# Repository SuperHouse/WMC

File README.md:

Wheelchair Motor Controller
===========================

Motion controller for an electric wheelchair using 24V DC motors, such
as a Permobil F5.

Controls two wheelchair motors using a RoboClaw motor driver. It also
has outputs for a solenoid braking system, and a CAN bus interface to
communicate with other modules on the chair.

Features:

 * Takes power from the chair battery.
 * Mounting location for RoboClaw motor driver.
 * Communicates with RoboClaw using serial commands.
 * MOSFETs to release mechanical brakes.
 * CAN bus.

More information is available at:

  https://www.superhouse.tv/wmc

Hardware
--------
The "Hardware" directory contains the PCB design as an EAGLE project.
EAGLE PCB design software is available from Autodesk free for
non-commercial use.

Firmware
--------
The "Firmware" directory contains example firmware as an Arduino
project.

Credits
-------
 * Jonathan Oxer <jon@oxer.com.au>
 * Chris Fryer <chris.fryer78@gmail.com>

License
-------
Copyright 2019-2020 SuperHouse Automation Pty Ltd  www.superhouse.tv  

The hardware portion of this project is licensed under the TAPR Open
Hardware License (www.tapr.org/OHL). The "license" folder within this
repository contains a copy of this license in plain text format.

The software portion of this project is licensed under the Simplified
BSD License. The "licence" folder within this project contains a
copy of this license in plain text format.

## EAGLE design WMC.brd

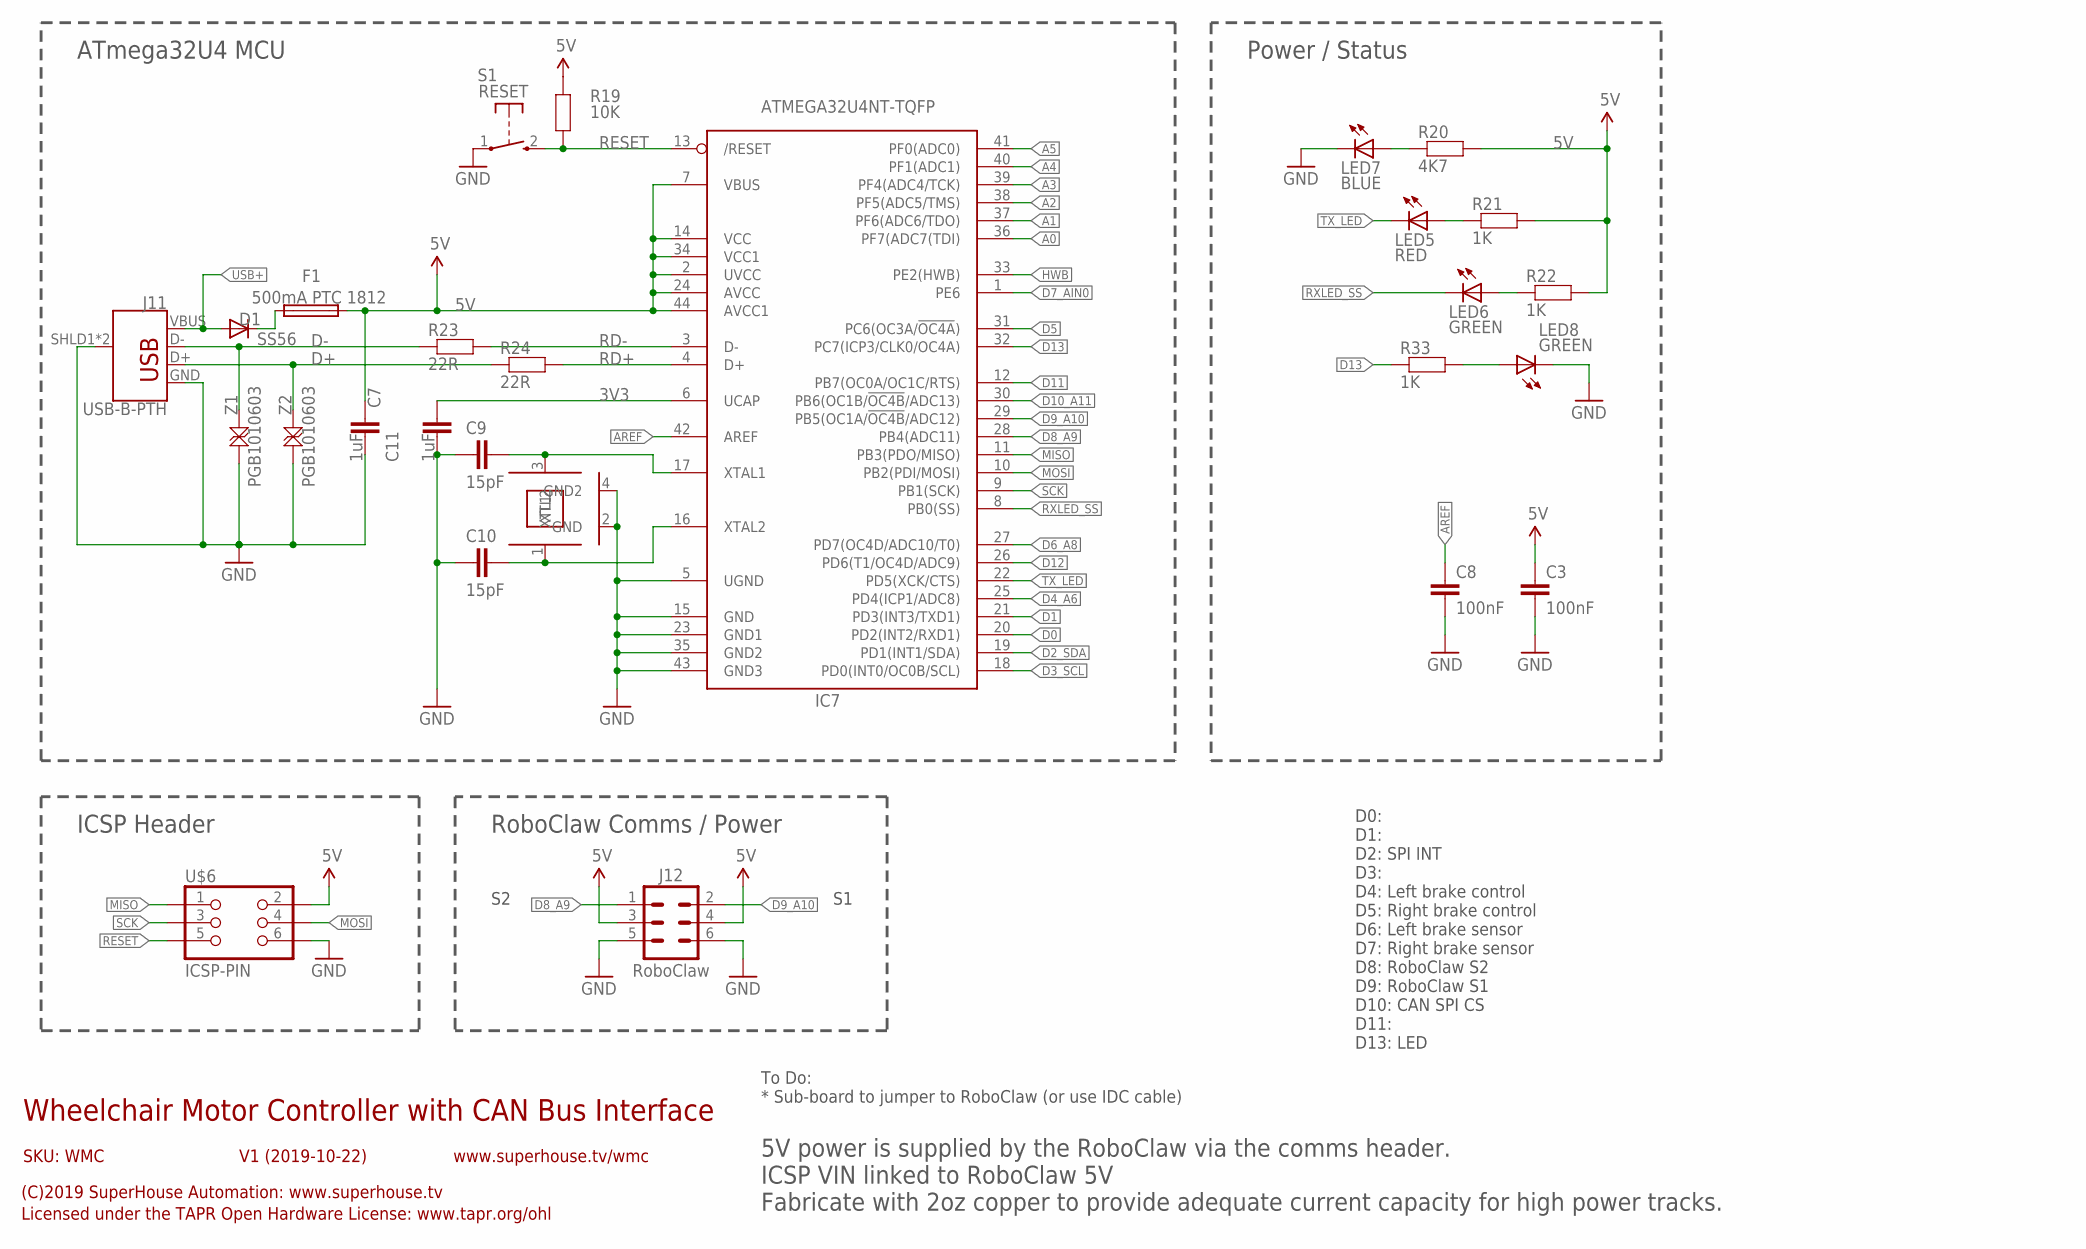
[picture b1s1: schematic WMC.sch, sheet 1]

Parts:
C3, C8: 100nF; C0603
C7, C11: 1uF; C0603
C9, C10: 15pF; C0603
D1: SS56; SMA-DIODE
F1: 500mA PTC 1812; 1812
IC7: ATMEGA32U4NT-TQFP; TQFP44
J11: USB-B-PTH
J12: RoboClaw; 2X03-P
LED5: RED; LED-0603
LED6, LED8: GREEN; LED-0603
LED7: BLUE; LED-0603
R19: 10K; R0603
R20: 4K7; R0603
R21, R22, R33: 1K; R0603
R23, R24: 22R; R0603
S1: RESET; TACTILE_SMT_3X4X2
U$6: ICSP-PIN; 2X03-ICSP
XTL2: 16MHz; CRYSTAL-SMD-3X2
Z1, Z2: PGB1010603; TVS0603

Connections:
3V3: C11.2, IC7.6 (UCAP)
5V: C3.1, C7.1, F1.2, IC7.2 (UVCC), IC7.7 (VBUS), IC7.14 (VCC), IC7.24 (AVCC), IC7.34 (VCC1), IC7.44 (AVCC1), J12.3, J12.4, R19.2, R20.2, R21.2, R22.2, U$6.2; also elsewhere on the board
A0: IC7.36 (PF7(ADC7(TDI))
A1: IC7.37 (PF6(ADC6/TDO))
A2: IC7.38 (PF5(ADC5/TMS))
A3: IC7.39 (PF4(ADC4/TCK))
A4: IC7.40 (PF1(ADC1))
A5: IC7.41 (PF0(ADC0))
AREF: C8.1, IC7.42 (AREF)
D0: IC7.20 (PD2(INT2/RXD1))
D1: IC7.21 (PD3(INT3/TXD1))
D2_SDA: IC7.19 (PD1(INT1/SDA)); also elsewhere on the board
D3_SCL: IC7.18 (PD0(INT0/OC0B/SCL))
D4_A6: IC7.25 (PD4(ICP1/ADC8)); also elsewhere on the board
D5: IC7.31 (PC6(OC3A/!OC4A!)); also elsewhere on the board
D6_A8: IC7.27 (PD7(OC4D/ADC10/T0)); also elsewhere on the board
D7_AIN0: IC7.1 (PE6); also elsewhere on the board
D8_A9: IC7.28 (PB4(ADC11)), J12.1
D9_A10: IC7.29 (PB5(OC1A/!OC4B!/ADC12)), J12.2
D10_A11: IC7.30 (PB6(OC1B/!OC4B!/ADC13)); also elsewhere on the board
D11: IC7.12 (PB7(OC0A/OC1C/RTS))
D12: IC7.26 (PD6(T1/OC4D/ADC9))
D13: IC7.32 (PC7(ICP3/CLK0/OC4A)), R33.1
D+: J11.D+, R24.1, Z2.2
D-: J11.D-, R23.1, Z1.2
GND: C3.2, C7.2, C8.2, C9.1, C10.1, C11.1, IC7.5 (UGND), IC7.15 (GND), IC7.23 (GND1), IC7.35 (GND2), IC7.43 (GND3), J11.GND, J11.SHLD1 (SHIELD), J11.SHLD2 (SHIELD), J12.5, J12.6, LED7.C, LED8.C, S1.1, U$6.6, XTL2.2 (GND), XTL2.4 (GND2), Z1.1, Z2.1; also elsewhere on the board
HWB: IC7.33 (PE2(HWB))
MISO: IC7.11 (PB3(PDO/MISO)), U$6.1; also elsewhere on the board
MOSI: IC7.10 (PB2(PDI/MOSI)), U$6.4; also elsewhere on the board
unnamed: C9.2, IC7.17 (XTAL1), XTL2.3 (XTL2)
unnamed: C10.2, IC7.16 (XTAL2), XTL2.1 (XTL1)
unnamed: LED7.A, R20.1
unnamed: LED5.A, R21.1
unnamed: LED6.A, R22.1
unnamed: D1.C, F1.1
unnamed: LED8.A, R33.2
RD+: IC7.4 (D+), R24.2
RD-: IC7.3 (D-), R23.2
RESET: IC7.13 (/RESET), R19.1, S1.2 (S), U$6.5
RXLED_SS: IC7.8 (PB0(SS)), LED6.C
SCK: IC7.9 (PB1(SCK)), U$6.3; also elsewhere on the board
TX_LED: IC7.22 (PD5(XCK/CTS)), LED5.C
USB+: D1.A, J11.VBUS

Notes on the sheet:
Wheelchair Motor Controller with CAN Bus Interface
V1 (2019-10-22)
SKU: WMC
(C)2019 SuperHouse Automation: www.superhouse.tv
Licensed under the TAPR Open Hardware License: www.tapr.org/ohl
www.superhouse.tv/wmc
To Do: * Sub-board to jumper to RoboClaw (or use IDC cable)
ATmega32U4 MCU
Power / Status
ICSP Header
RoboClaw Comms / Power
5V power is supplied by the RoboClaw via the comms header. ICSP VIN linked to RoboClaw 5V Fabricate with 2oz copper to provide adequate current capacity for high power tracks.
D0: D1: D2: SPI INT D3: D4: Left brake control D5: Right brake control D6: Left brake sensor D7: Right brake sensor D8: RoboClaw S2 D9: RoboClaw S1 D10: CAN SPI CS D11: D13: LED

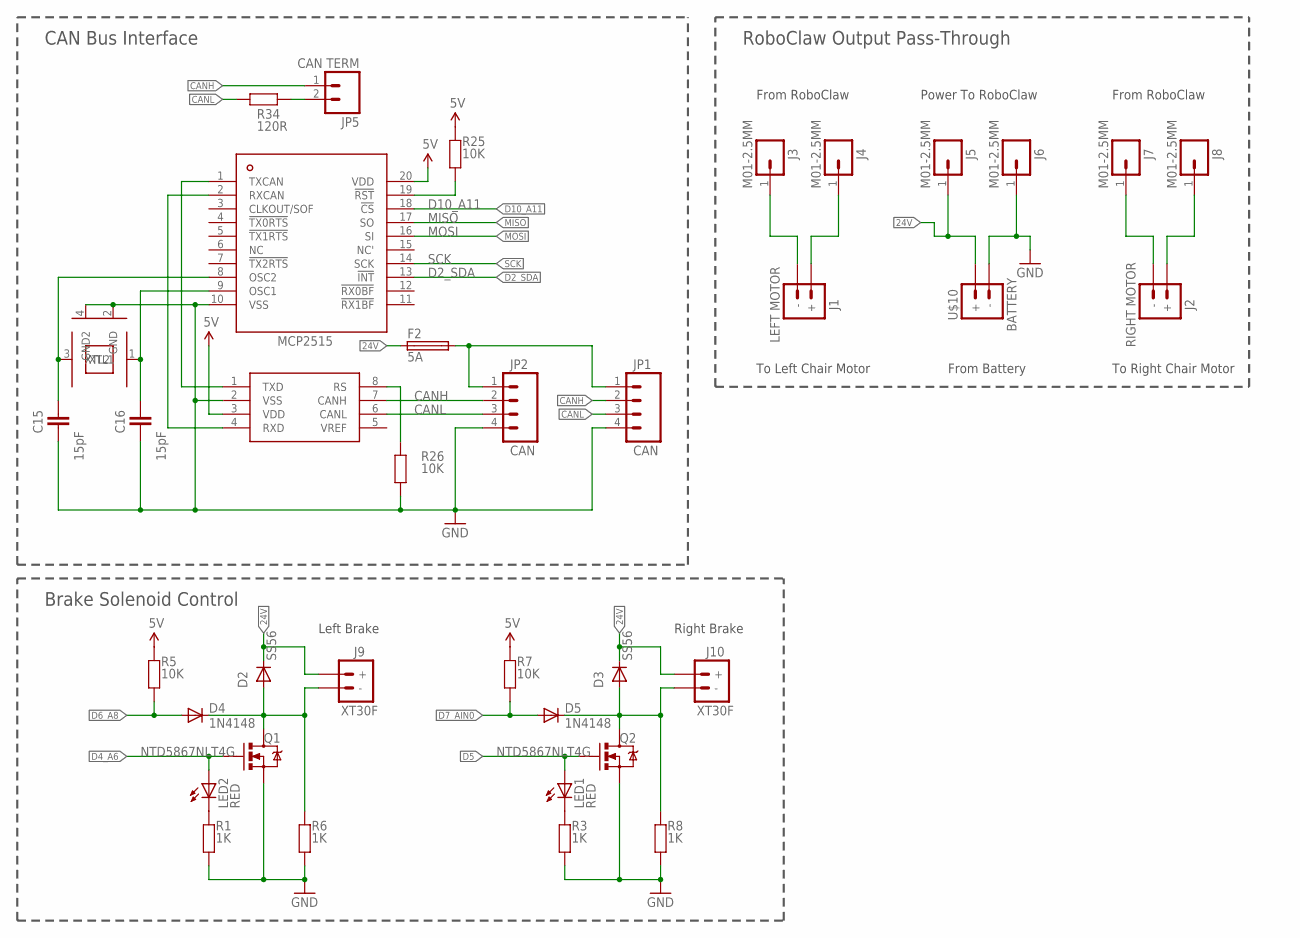
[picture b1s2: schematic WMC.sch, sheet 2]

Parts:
C15, C16: 15pF; C0603
D2, D3: SS56; SMA-DIODE
D4, D5: 1N4148; SOD-323
F2: 5A; MCCQ-122
IC5: MCP2551; SO08
IC6: MCP2515; TSSOP20
J1: LEFT MOTOR; XT60PW-F
J2: RIGHT MOTOR; XT60PW-F
J3, J4, J5, J6, J7, J8: M01-2.5MM; 1X01-2.5MM
J9, J10: XT30F; XT30PW-F
JP1, JP2: CAN; 1X04-P
JP5: CAN TERM; 1X02-P
LED1, LED2: RED; LED-0603
Q1, Q2: NTD5867NLT4G; DPACK
R1, R3, R6, R8: 1K; R0603
R5, R7, R25, R26: 10K; R0603
R34: 120R; R0603
U$10: BATTERY; XT90PW-M
XTL4: 16MHz; CRYSTAL-SMD-3X2

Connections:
5V: IC5.3 (VDD), IC6.20 (VDD), R5.2, R7.2, R25.2; also elsewhere on the board
24V: D2.C, D3.C, F2.1, F2.2 (1), J5.1, J9.+, J10.+, U$10.+
CANH: IC5.7 (CANH), JP1.2, JP2.2, JP5.1
CANL: IC5.6 (CANL), JP1.3, JP2.3, R34.1
D2_SDA: IC6.13 (!INT); also elsewhere on the board
D4_A6: LED2.A, Q1.1 (G); also elsewhere on the board
D5: LED1.A, Q2.1 (G); also elsewhere on the board
D6_A8: D4.2 (A), R5.1; also elsewhere on the board
D7_AIN0: D5.2 (A), R7.1; also elsewhere on the board
D10_A11: IC6.18 (!CS); also elsewhere on the board
GND: C15.1, C16.1, IC5.2 (VSS), IC6.10 (VSS), J6.1, JP1.4, JP2.4, Q1.3 (S), Q2.3 (S), R1.1, R3.1, R6.1, R8.1, R26.1, U$10.-, XTL4.2 (GND), XTL4.4 (GND2); also elsewhere on the board
LEFT_BRAKE: D2.A, D4.1 (C), J9.-, Q1.2 (D), R6.2
MISO: IC6.17 (SO); also elsewhere on the board
MOSI: IC6.16 (SI); also elsewhere on the board
unnamed: LED2.C, R1.2
unnamed: F2.3 (2), F2.4 (2), JP1.1, JP2.1
unnamed: J1.+, J4.1
unnamed: LED1.C, R3.2
unnamed: J1.-, J3.1
unnamed: J2.-, J7.1
unnamed: J2.+, J8.1
unnamed: IC6.19 (!RST), R25.1
unnamed: IC5.1 (TXD), IC6.1 (TXCAN)
unnamed: IC5.4 (RXD), IC6.2 (RXCAN)
unnamed: IC5.8 (RS), R26.2
unnamed: C15.2, IC6.8 (OSC2), XTL4.3 (XTL2)
unnamed: C16.2, IC6.9 (OSC1), XTL4.1 (XTL1)
unnamed: JP5.2, R34.2
RIGHT_BRAKE: D3.A, D5.1 (C), J10.-, Q2.2 (D), R8.2
SCK: IC6.14 (SCK); also elsewhere on the board

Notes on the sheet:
RoboClaw Output Pass-Through
CAN Bus Interface
Brake Solenoid Control
Left Brake
Right Brake
From RoboClaw
From Battery
To Right Chair Motor
To Left Chair Motor
Power To RoboClaw

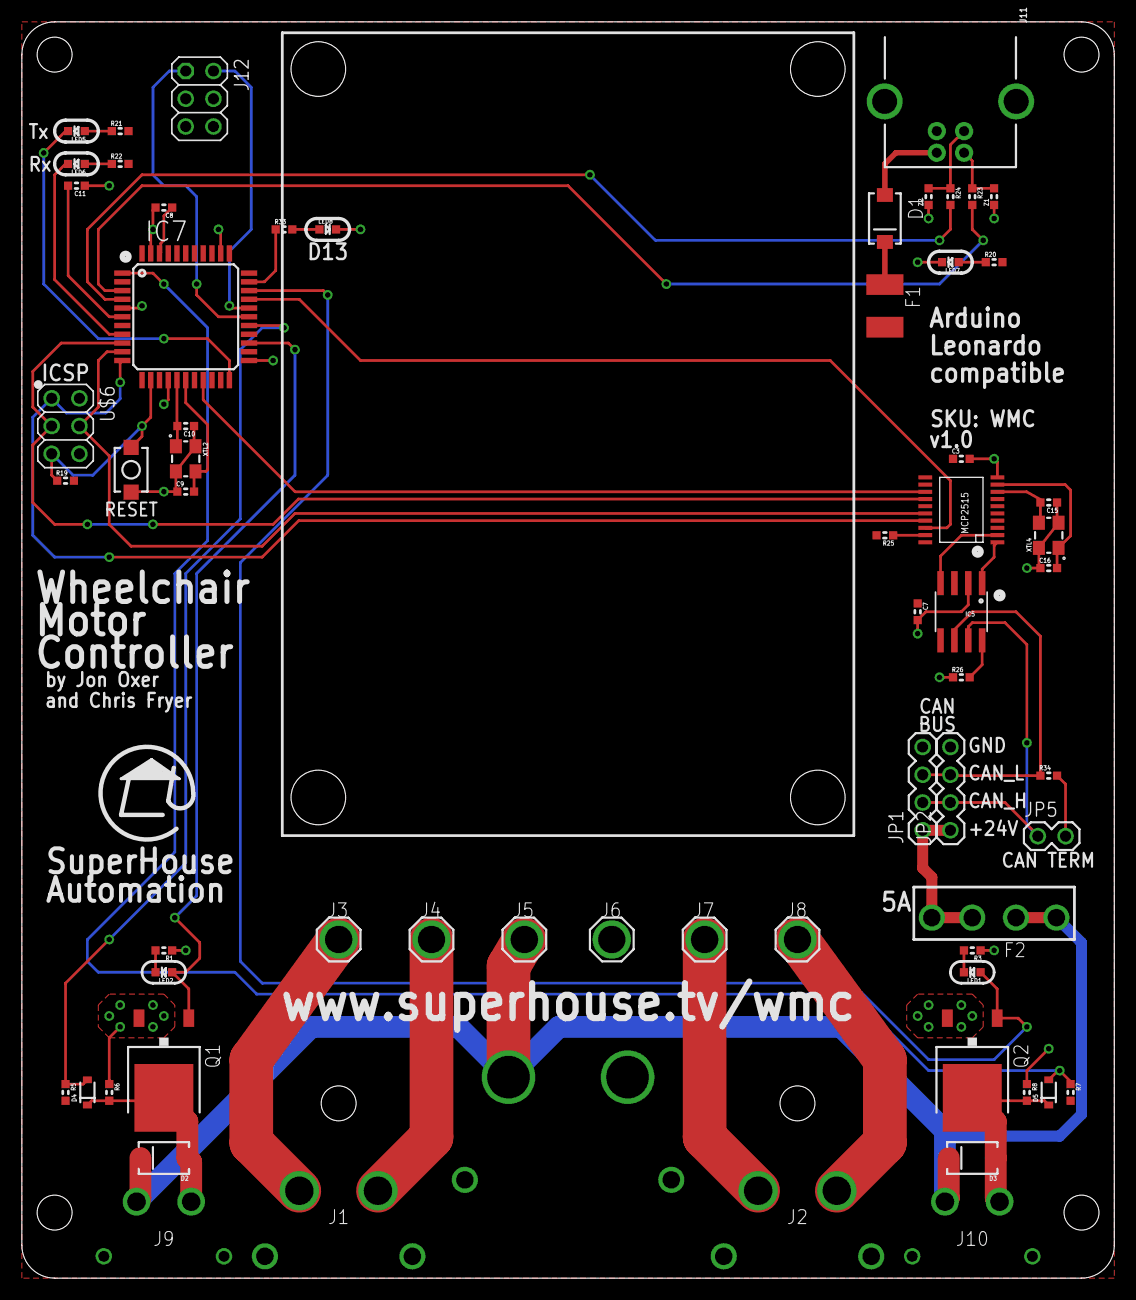
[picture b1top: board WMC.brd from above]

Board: 2 copper layers, 100.0 x 115.0 mm, 64 parts (0 on the bottom side), 50 nets.

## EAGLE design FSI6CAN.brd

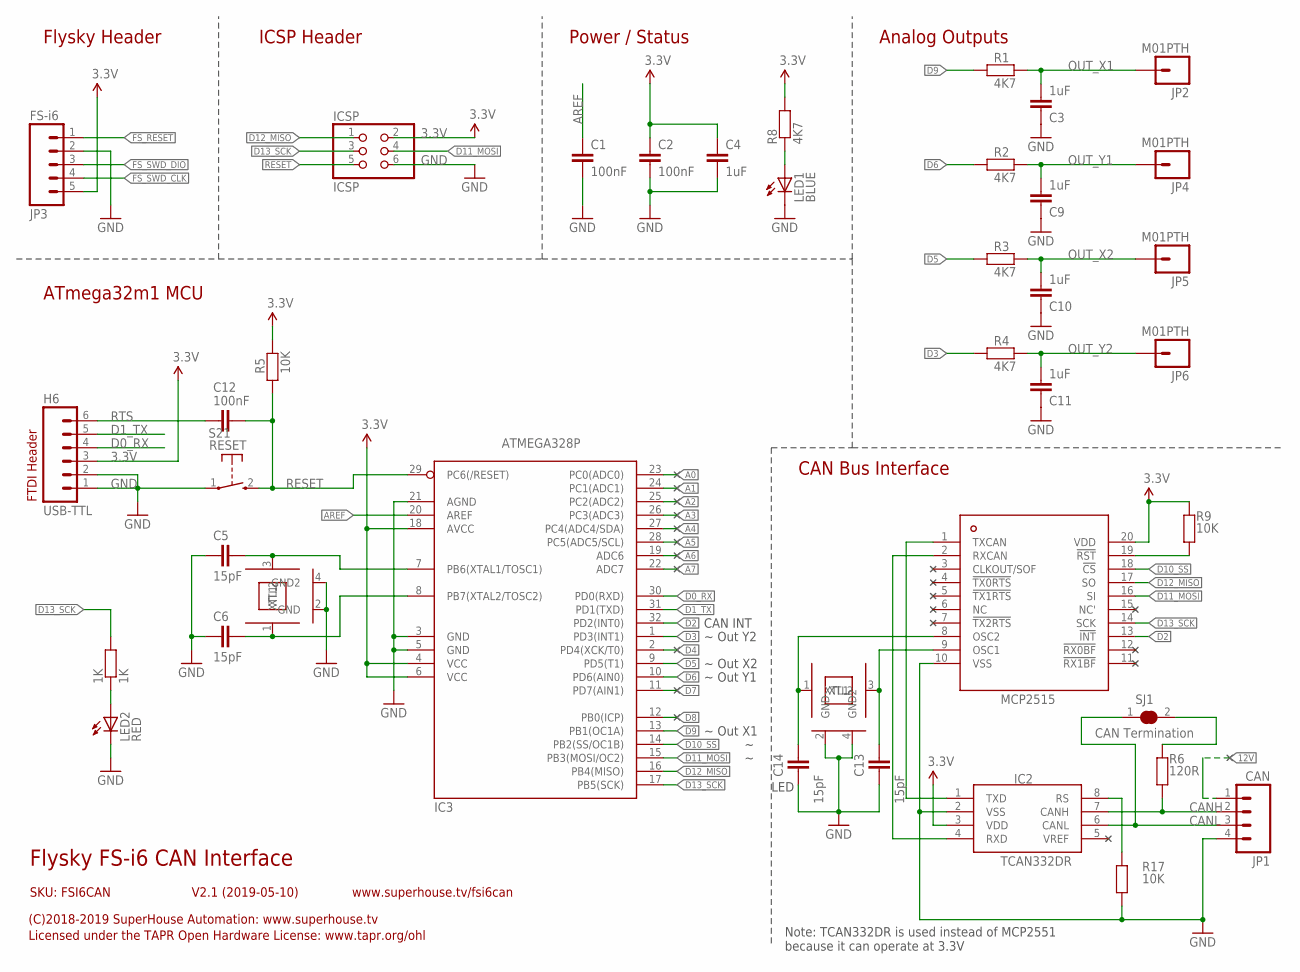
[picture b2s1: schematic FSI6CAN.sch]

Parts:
1K: 1K; R0603
C1: 100nF; C0603
C2, C12: 100nF; 0603
C3, C9, C10, C11: 1uF; C0603
C4: 1uF; 0603
C5, C6, C13, C14: 15pF; C0603
H6: USB-TTL; 1X06
IC2: TCAN332DR; SO08
IC3: ATMEGA328P; TQFP32-08
IC4: MCP2515; TSSOP20
ICSP: ICSP; 2X03
JP1: CAN; 1X04
JP2, JP4, JP5, JP6: M01PTH; 1X01
JP3: FS-i6; 1X05
LED1: BLUE; LED-0603
LED2: RED; LED-0603
R1, R2, R3, R4: 4K7; R0603
R5: 10K; 0603
R6: 120R; 0603
R8: 4K7; 0603
R9, R17: 10K; R0603
S21: RESET; TACTILE_SMT_3X4X2
SJ1: CAN Termination; SJC
XTL1: 8MHz; CRYSTAL-SMD-3X2
XTL3: 16MHz; CRYSTAL-SMD-3X2

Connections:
3.3V: C2.1, C4.1, H6.3, IC2.3 (VDD), IC3.4 (VCC), IC3.6 (VCC), IC3.18 (AVCC), IC4.20 (VDD), ICSP.2, JP3.5, R5.1, R8.2, R9.2
12V: JP1.1
A0: IC3.23 (PC0(ADC0))
A1: IC3.24 (PC1(ADC1))
A2: IC3.25 (PC2(ADC2))
A3: IC3.26 (PC3(ADC3))
A4: IC3.27 (PC4(ADC4/SDA))
A5: IC3.28 (PC5(ADC5/SCL))
A6: IC3.19 (ADC6)
A7: IC3.22 (ADC7)
AREF: C1.1, IC3.20 (AREF)
CANH: IC2.7 (CANH), JP1.2, R6.1
CANL: IC2.6 (CANL), JP1.3, SJ1.1
D0_RX: H6.4, IC3.30 (PD0(RXD))
D1_TX: H6.5, IC3.31 (PD1(TXD))
D2: IC3.32 (PD2(INT0)), IC4.13 (!INT)
D3: IC3.1 (PD3(INT1)), R4.1
D4: IC3.2 (PD4(XCK/T0))
D5: IC3.9 (PD5(T1)), R3.1
D6: IC3.10 (PD6(AIN0)), R2.1
D7: IC3.11 (PD7(AIN1))
D8: IC3.12 (PB0(ICP))
D9: IC3.13 (PB1(OC1A)), R1.1
D10_SS: IC3.14 (PB2(SS/OC1B)), IC4.18 (!CS)
D11_MOSI: IC3.15 (PB3(MOSI/OC2)), IC4.16 (SI), ICSP.4
D12_MISO: IC3.16 (PB4(MISO)), IC4.17 (SO), ICSP.1
D13_SCK: 1K.2, IC3.17 (PB5(SCK)), IC4.14 (SCK), ICSP.3
FS_RESET: JP3.1
FS_SWD_CLK: JP3.4
FS_SWD_DIO: JP3.3
GND: C1.2, C2.2, C3.2, C4.2, C5.1, C6.1, C9.2, C10.2, C11.2, C13.1, C14.1, H6.1, H6.2, IC2.2 (VSS), IC3.3 (GND), IC3.5 (GND), IC3.21 (AGND), IC4.10 (VSS), ICSP.6, JP1.4, JP3.2, LED1.C, LED2.C, R17.1, S21.1, XTL1.2 (GND), XTL1.4 (GND2), XTL3.2 (GND), XTL3.4 (GND2)
unnamed: 1K.1, LED2.A
unnamed: R6.2, SJ1.2
unnamed: IC2.1 (TXD), IC4.1 (TXCAN)
unnamed: LED1.A, R8.1
unnamed: IC2.4 (RXD), IC4.2 (RXCAN)
unnamed: C13.2, IC4.9 (OSC1), XTL3.3 (XTL2)
unnamed: C14.2, IC4.8 (OSC2), XTL3.1 (XTL1)
unnamed: C5.2, IC3.7 (PB6(XTAL1/TOSC1)), XTL1.3 (XTL2)
unnamed: C6.2, IC3.8 (PB7(XTAL2/TOSC2)), XTL1.1 (XTL1)
unnamed: IC2.8 (RS), R17.2
unnamed: IC4.19 (!RST), R9.1
OUT_X1: C3.1, JP2.1, R1.2
OUT_X2: C10.1, JP5.1, R3.2
OUT_Y1: C9.1, JP4.1, R2.2
OUT_Y2: C11.1, JP6.1, R4.2
RESET: C12.2, IC3.29 (PC6(/RESET)), ICSP.5, R5.2, S21.2 (S)
RTS: C12.1, H6.6

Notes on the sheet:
ATmega32m1 MCU
Flysky FS-i6 CAN Interface
V2.1 (2019-05-10)
SKU: FSI6CAN
(C)2018-2019 SuperHouse Automation: www.superhouse.tv
Licensed under the TAPR Open Hardware License: www.tapr.org/ohl
www.superhouse.tv/fsi6can
Power / Status
FTDI Header
Flysky Header
Analog Outputs
CAN Bus Interface
ICSP Header
~ Out Y2
~ Out X2
~ Out Y1
LED
Note: TCAN332DR is used instead of MCP2551 because it can operate at 3.3V
CAN INT
~ Out X1

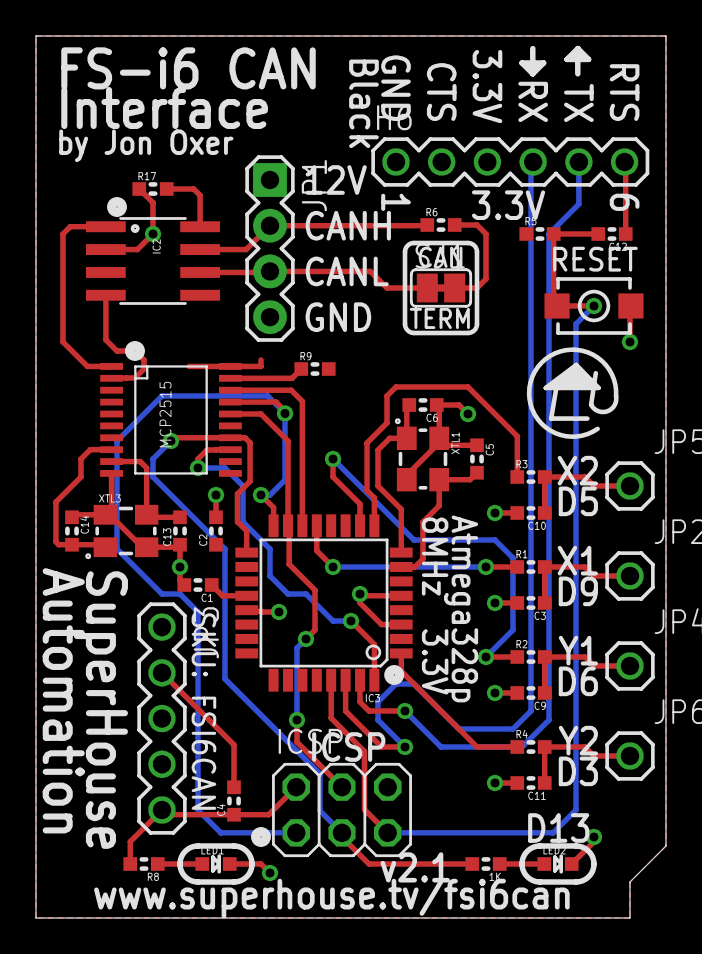
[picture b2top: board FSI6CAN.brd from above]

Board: 2 copper layers, 35.0 x 49.0 mm, 39 parts (0 on the bottom side), 33 nets.

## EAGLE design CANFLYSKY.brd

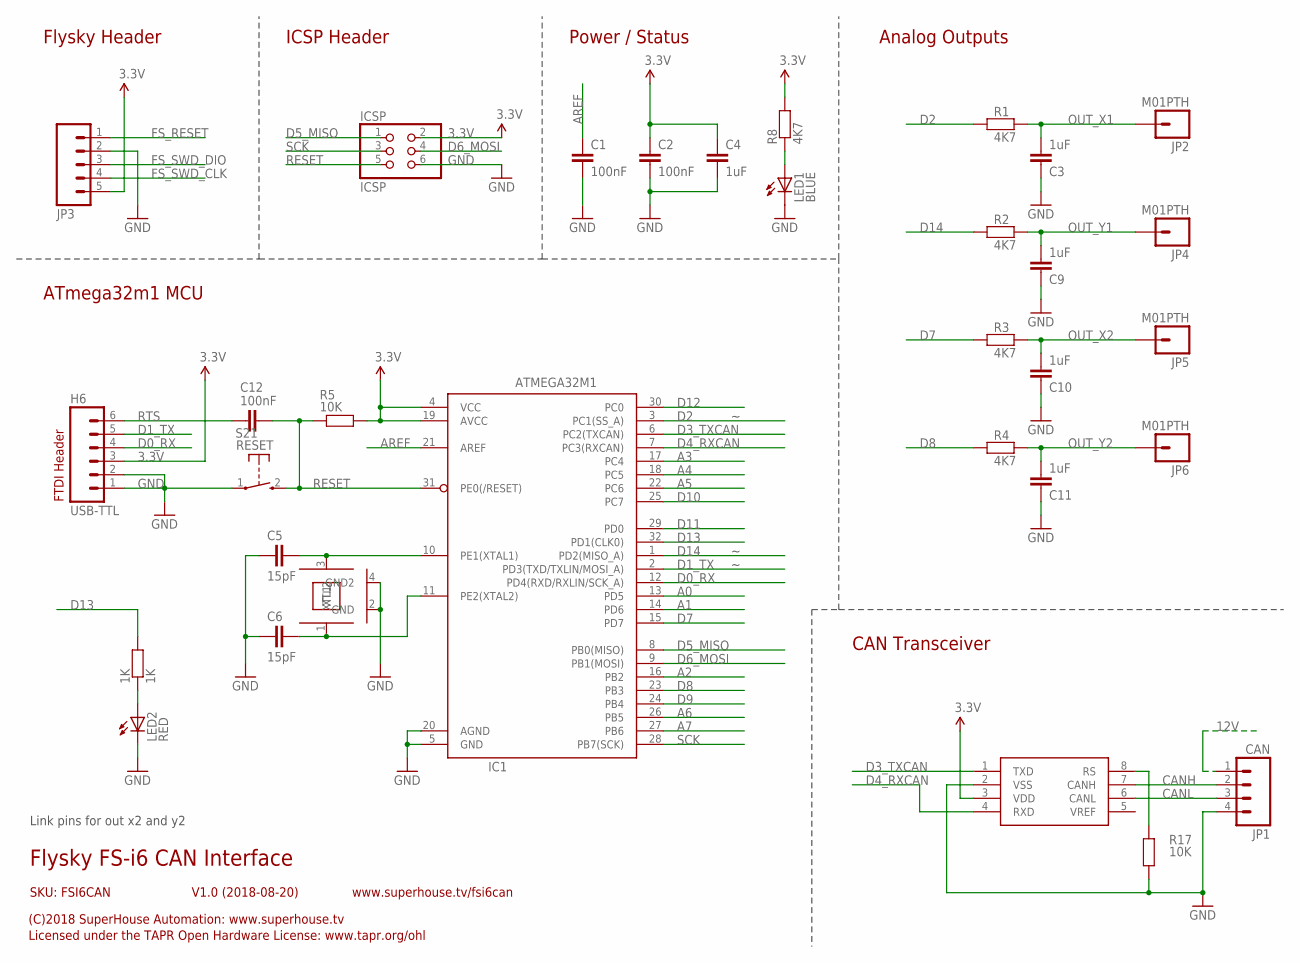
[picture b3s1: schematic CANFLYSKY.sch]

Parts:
1K: 1K; 0603
C1, C2, C12: 100nF; 0603
C3, C4, C9, C10, C11: 1uF; 0603
C5, C6: 15pF; 0603
H6: USB-TTL; 1X06
IC1: ATMEGA32M1; TQFP32-08
ICSP: ICSP; 2X03
JP1: CAN; 1X04
JP2, JP4, JP5, JP6: M01PTH; 1X01
JP3: M05PTH; 1X05
LED1: BLUE; LED-0603
LED2: RED; LED-0603
R1, R2, R3, R4, R8: 4K7; 0603
R5, R17: 10K; 0603
S21: RESET; TACTILE_SWITCH_SMD_2PIN_TINY
U1: MCP2551; SO08
XTL1: 8MHz; CRYSTAL-SMD-3X2

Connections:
3.3V: C2.1, C4.1, H6.3, IC1.4 (VCC), IC1.19 (AVCC), ICSP.2, JP3.5, R5.1, R8.2, U1.3 (VDD)
12V: JP1.1
A0: IC1.13 (PD5)
A1: IC1.14 (PD6)
A2: IC1.16 (PB2)
A3: IC1.17 (PC4)
A4: IC1.18 (PC5)
A5: IC1.22 (PC6)
A6: IC1.26 (PB5)
A7: IC1.27 (PB6)
AREF: C1.1, IC1.21 (AREF)
CANH: JP1.2, U1.7 (CANH)
CANL: JP1.3, U1.6 (CANL)
D0_RX: H6.4, IC1.12 (PD4(RXD/RXLIN/SCK_A))
D1_TX: H6.5, IC1.2 (PD3(TXD/TXLIN/MOSI_A))
D2: IC1.3 (PC1(SS_A)), R1.1
D3_TXCAN: IC1.6 (PC2(TXCAN)), U1.1 (TXD)
D4_RXCAN: IC1.7 (PC3(RXCAN)), U1.4 (RXD)
D5_MISO: IC1.8 (PB0(MISO)), ICSP.1
D6_MOSI: IC1.9 (PB1(MOSI)), ICSP.4
D7: IC1.15 (PD7), R3.1
D8: IC1.23 (PB3), R4.1
D9: IC1.24 (PB4)
D10: IC1.25 (PC7)
D11: IC1.29 (PD0)
D12: IC1.30 (PC0)
D13: 1K.2, IC1.32 (PD1(CLK0))
D14: IC1.1 (PD2(MISO_A)), R2.1
FS_RESET: JP3.1
FS_SWD_CLK: JP3.4
FS_SWD_DIO: JP3.3
GND: C1.2, C2.2, C3.2, C4.2, C5.1, C6.1, C9.2, C10.2, C11.2, H6.1, H6.2, IC1.5 (GND), IC1.20 (AGND), ICSP.6, JP1.4, JP3.2, LED1.C, LED2.C, R17.1, S21.1, U1.2 (VSS), XTL1.2 (GND), XTL1.4 (GND2)
unnamed: 1K.1, LED2.A
unnamed: LED1.A, R8.1
unnamed: C5.2, IC1.10 (PE1(XTAL1)), XTL1.3 (XTL2)
unnamed: C6.2, IC1.11 (PE2(XTAL2)), XTL1.1 (XTL1)
unnamed: R17.2, U1.8 (RS)
OUT_X1: C3.1, JP2.1, R1.2
OUT_X2: C10.1, JP5.1, R3.2
OUT_Y1: C9.1, JP4.1, R2.2
OUT_Y2: C11.1, JP6.1, R4.2
RESET: C12.2, IC1.31 (PE0(/RESET)), ICSP.5, R5.2, S21.2 (S)
RTS: C12.1, H6.6
SCK: IC1.28 (PB7(SCK)), ICSP.3

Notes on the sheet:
ATmega32m1 MCU
Flysky FS-i6 CAN Interface
V1.0 (2018-08-20)
SKU: FSI6CAN
(C)2018 SuperHouse Automation: www.superhouse.tv
Licensed under the TAPR Open Hardware License: www.tapr.org/ohl
www.superhouse.tv/fsi6can
Power / Status
FTDI Header
Flysky Header
Analog Outputs
CAN Transceiver
ICSP Header
Link pins for out x2 and y2

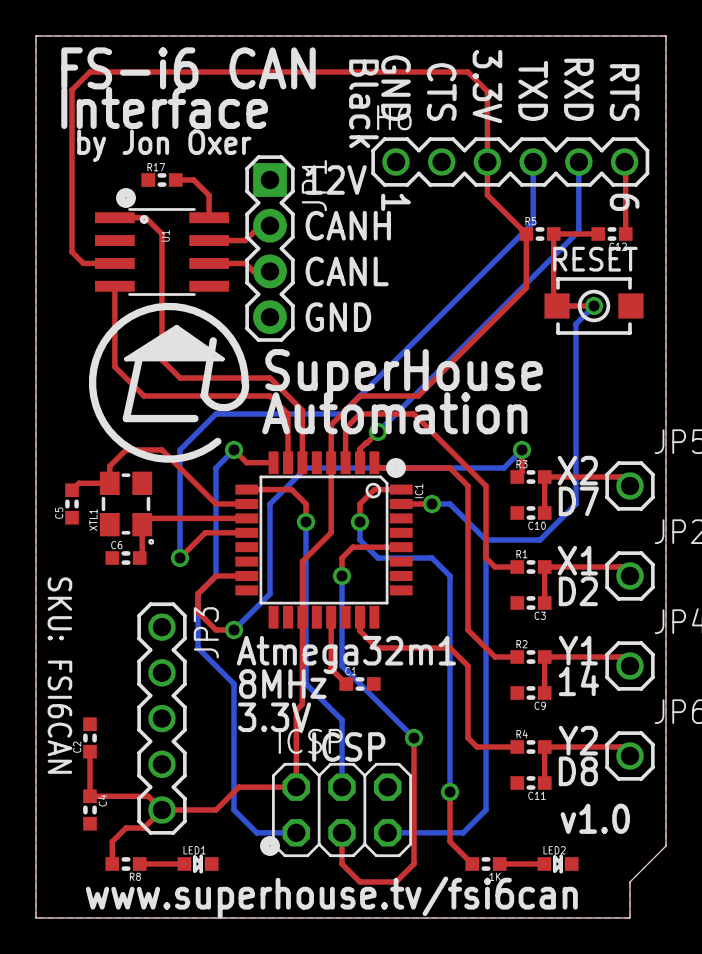
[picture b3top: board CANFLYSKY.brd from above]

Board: 2 copper layers, 35.0 x 49.0 mm, 32 parts (0 on the bottom side), 28 nets.

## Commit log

2018-08-20 Imported files from CBMINI project to begin conversion
2018-08-20 Removed unnecessary parts
2018-10-25 Completed initial routing
2018-10-26 Finished routing
2018-10-26 Updated README and renamed project files
2018-11-24 Improved designators
2019-04-23 Changed I/O pin for output Y2 and switch ICSP to other SPI port
2019-04-25 Added CAN termination
2019-04-25 Replaced MCP2551 with TCAN332DR
2019-05-02 Major rework using ATmega328p and MCP2515 for v2.0 release
2019-05-08 Improved designators for assembly
2019-05-10 Fixed silkscreen labels for outputs and for MCU orientation
2019-05-10 Fixed date
2019-09-17 Part replacement using SuperHouse libraries
2019-10-03 Renamed files migrated from FSI6CAN project
2019-10-06 Added XTxx external connections
2019-10-07 Major schematic replacement to switch to 32U4 processor
2019-10-08 Schematic cleanups and start of placement
2019-10-09 More routing
2019-10-15 Added brake status detection, finished routing
2019-10-21 Finished up silkscreen and routing
2019-10-21 Renamed project files
2019-10-21 Major mechanical restructure to mount RoboClaw on top of control board
2019-10-22 Routing, ERC, DRC for v1.0 release
2019-10-22 Added render to README
2019-10-22 Image size
2019-11-14 Initial import
2019-11-14 Added central dead spot to stop chair jittering at rest
2020-03-18 Changed lock status LEDs to green to indicate chair will move when locks released - green means go
2020-07-14 Moved files in preparation for merge
2020-07-14 Moved firmware
2020-07-14 Added license and merged READMEs
2020-07-14 Moved over files from old project
2020-07-14 Renamed example firmware
2020-07-14 Improved description
2020-07-14 Formatting

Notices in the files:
CANFLYSKY.brd:
(C)2018 SuperHouse Automation P/L
FSI6CAN.brd:
(C)2018-2019 SuperHouse Automation P/L
WMC.brd:
(C)2019 SuperHouse Automation P/L
parts and their libraries:
freetronics-original: Licensing: CC v3.0 Share-Alike You are welcome to use this library for commercial purposes.
